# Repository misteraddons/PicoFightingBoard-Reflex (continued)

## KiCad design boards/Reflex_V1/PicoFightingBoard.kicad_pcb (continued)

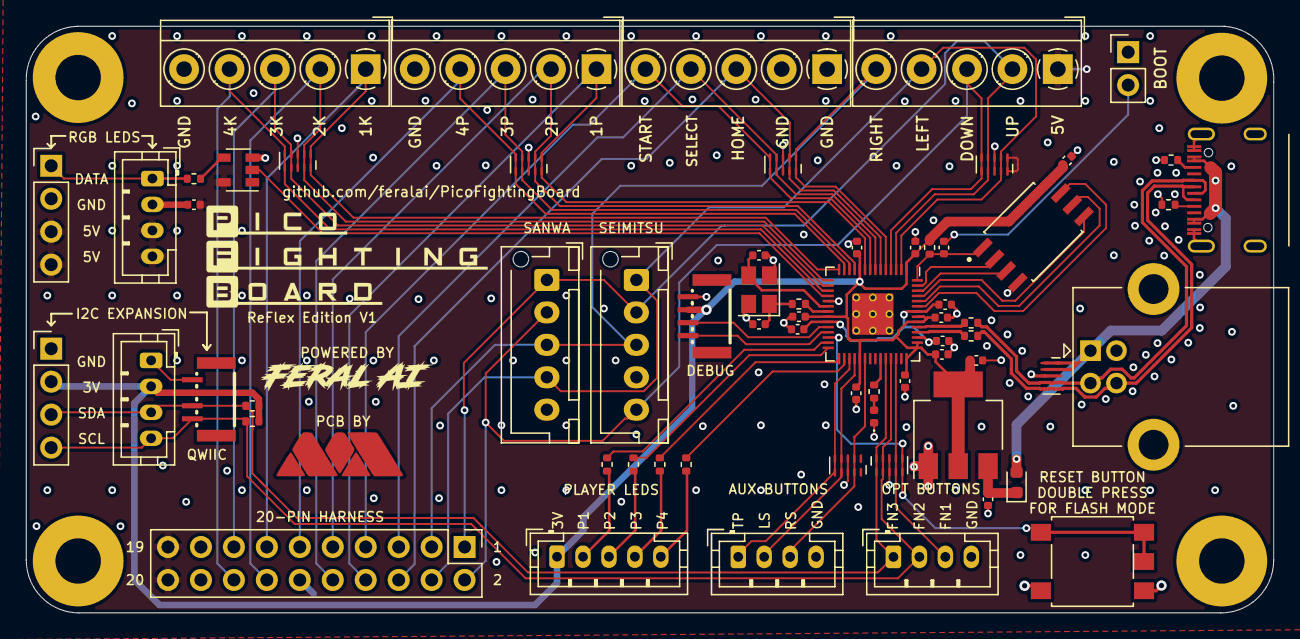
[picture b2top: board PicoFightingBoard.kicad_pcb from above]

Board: 4 copper layers, 96.1 x 45.2 mm, 71 parts (1 on the bottom side), 59 nets.

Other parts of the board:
Ref**: Val**; MiSTer_Addons_MA_10mm
Ref**#2: Val**; Idaho_M

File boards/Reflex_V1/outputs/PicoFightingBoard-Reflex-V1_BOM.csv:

Comment,Designator,Footprint,LCSC
SN74LV1T34DBV,U2,SOT-23-5,C100024
1K,"R14,R16",C_0402_1005Metric,C11702
LED 0402 YELLOW,D2,LED_0402_1005Metric,C130719
Conn_01x04_Male,"J1,J11,J12,J4",JST_PH_B4B-PH-K_1x04_P2.00mm_Vertical,C131334
SCHOTTKY DIODE,D1,D_0603_1608Metric,C143772
Conn_01x04_Male,"J13,J9",BOOM_SH_C145961_1x04_P1.00mm_Vertical,C145961
100n,"C1,C11,C13,C14,C15,C16,C5,C8,C9",C_0402_1005Metric,C1525
10u,"C17,C6,C7",C_0402_1005Metric,C15525
27p,"C3,C4",C_0402_1005Metric,C1557
Conn_01x05_Male,J3,JST_PH_B5B-PH-K_1x05_P2.00mm_Vertical,C157993
USB_C_Receptacle,J15,USB_Type_C_C167321,C167321
RP2040,U4,RP2040-QFN-56,C2040
27,"R18,R19",R_0402_1005Metric,C25100
330R,"R1,R2,R3,R4,R5",R_0402_1005Metric,C25104
470R,R20,R_0402_1005Metric,C25117
10K,R15,R_0402_1005Metric,C25744
4K7,"R6,R7",R_0402_1005Metric,C25900
5K1,"R21,R22",R_0402_1005Metric,C25905
SANWA,"J17,J18",JST_XH_B5B-XH-AM_1x05_P2.50mm_Vertical,C2908603
Conn_01x04_Male,"J10,J19",PinHeader_1x04_P2.54mm_Vertical,C2935910
TVS_RCLAMP0524P-N,"U1,U10,U5,U6,U7,U8,U9",UDFN-10_1.35x2.6mm_P0.5mm,C316044
ST01x05,"J5,J6,J7,J8",TerminalBlock_MetzConnect_Type059_RT06305HBWC_1x05_P3.50mm_Horizontal,C3646874
USB_B,J16,USB_B_Lumberg_2411_02_Horizontal,C388656
Conn_02x10_Odd_Even,J2,PinHeader_2x10_P2.54mm_Vertical,C492427
SW_Push,SW1,SW_SPST_6x6_C499305_C499302,C499305
1u,"C10,C12",C_0402_1005Metric,C52923
AMS1117-3.3,U3,SOT-223-3_TabPin2,C6186
W25Q16,FLASH1,SOIC127P790X216-8N,C82317
Crystal_GND24_Small,Y1,Crystal_SMD_SeikoEpson_TSX3225-4Pin_3.2x2.5mm,C9002
Conn_01x02,J14,PinHeader_1x02_P2.54mm_Vertical,

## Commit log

2022-11-21 Reflex Edition
    Placed RP2040 on main PCB
    Added TVS protection diodes
    Fixed mounting hole alignment
    Added 2.54mm pin headers for OLED and RGB LEDs
    Added Sanwa and Seimitsu headers for direct joystick connection
    Added USB-C connector
2023-01-10 Rename picture
2023-01-11 Rename Pico Fighting Board to Reflex Fighting Board
    Updated silkscreen, and Github link
2023-02-21 V1.1 Upload
2023-02-21 Remove extra files
2023-02-21 Rename Board Revisions
2023-02-21 Upload firmware and rename
2023-05-05 Update Pics
2023-09-09 Update revisions
2023-10-15 Reflex Encode V2 Source
